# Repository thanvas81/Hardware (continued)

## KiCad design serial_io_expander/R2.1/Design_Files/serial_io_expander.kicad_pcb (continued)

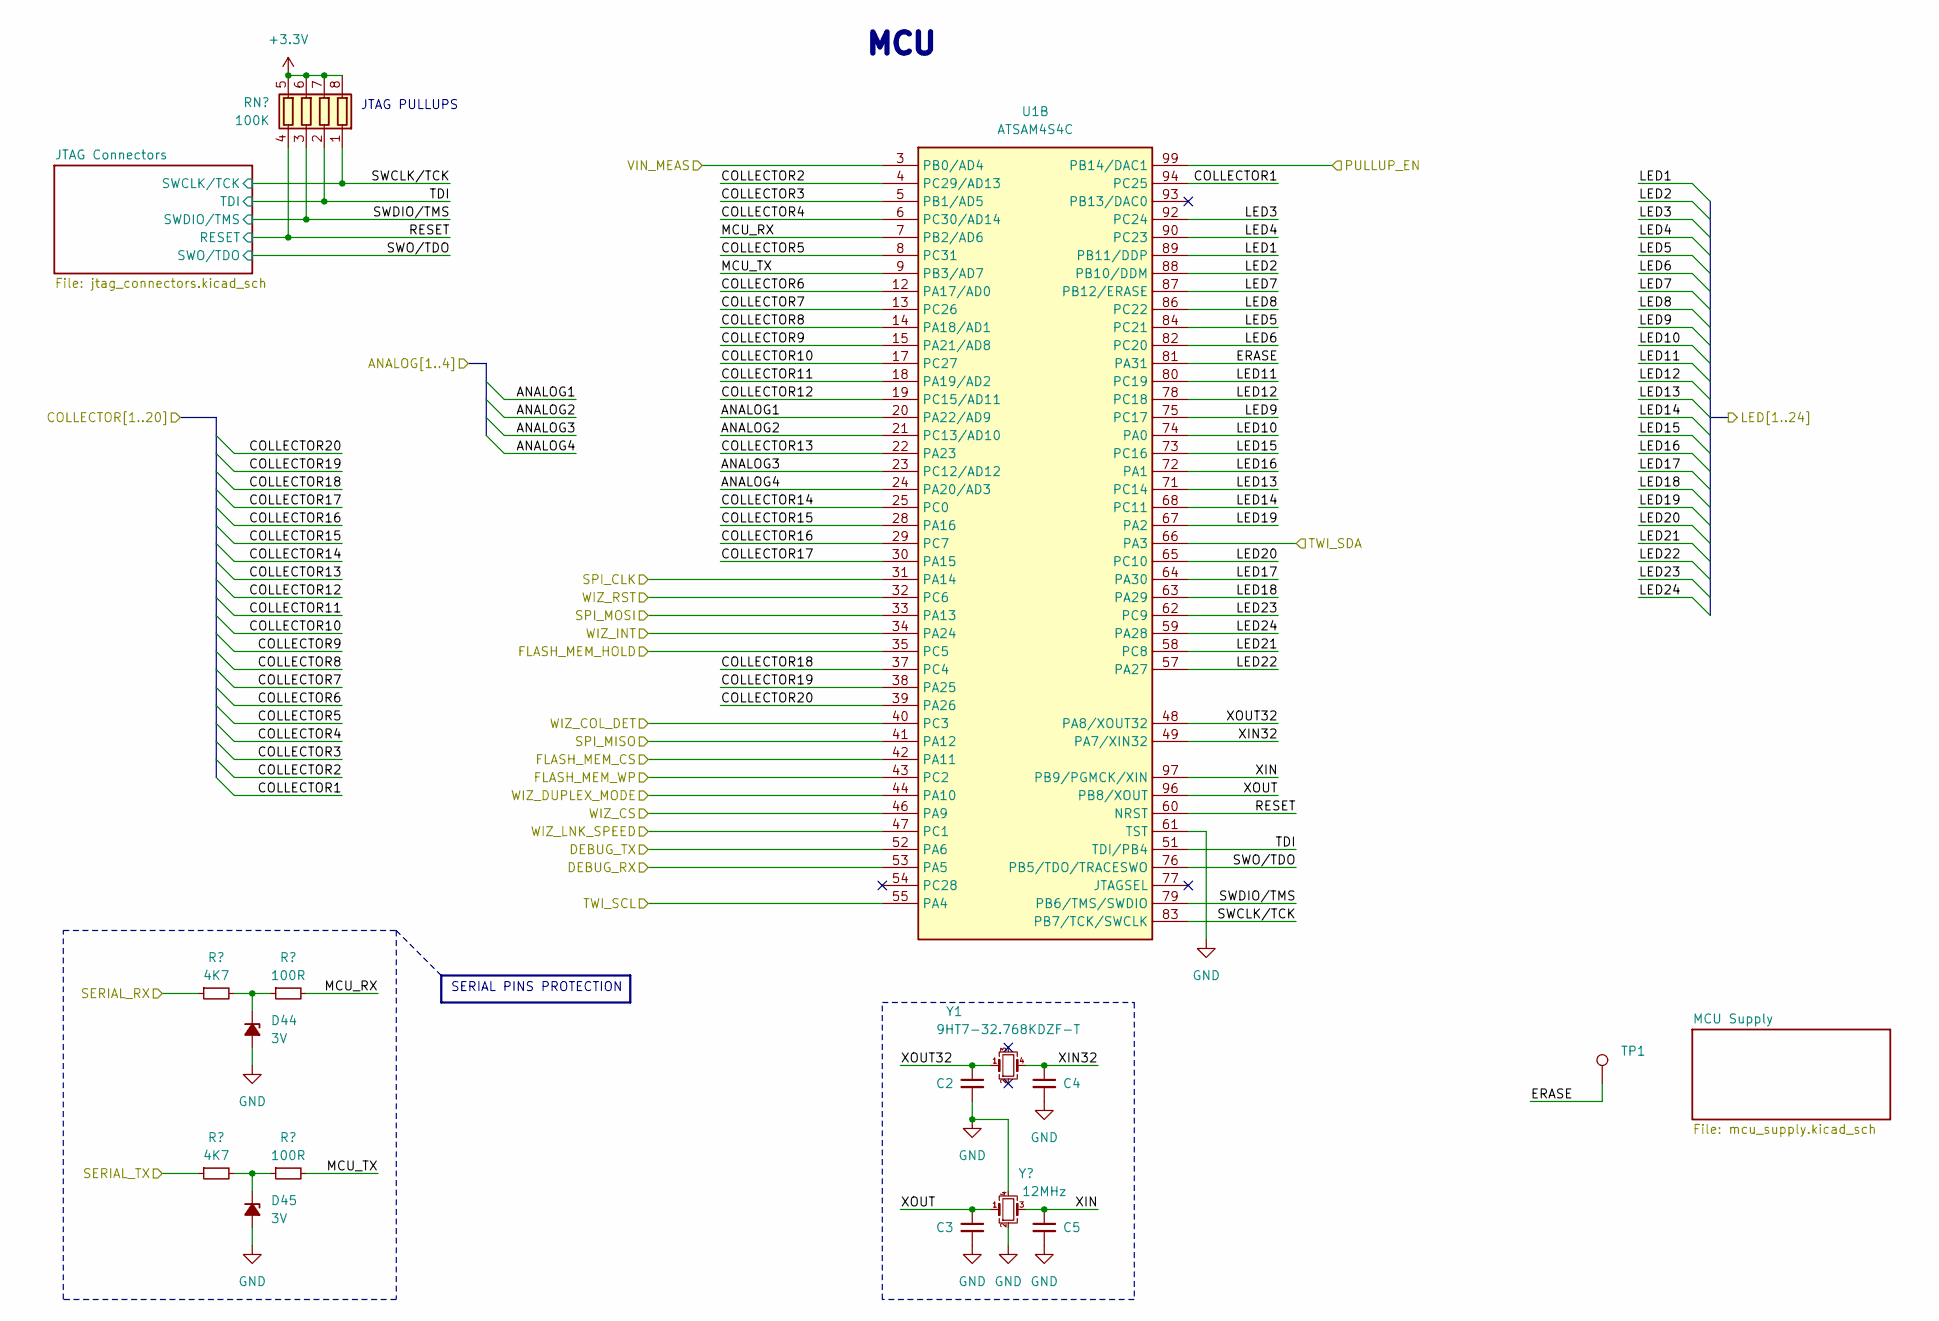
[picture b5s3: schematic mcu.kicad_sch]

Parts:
C2, C3, C4, C5: C_0603_1608Metric
D44, D45: 3V; D_SOD-123; PartkeeprID 75
R72, R73: 4K7; R_0603_1608Metric
R74, R75: 100R; R_0603_1608Metric
RN2: 100K; R_Array_Concave_4x0603
TP1: TestPoint; TestPoint_Pad_D1.5mm
U1: ATSAM4S4C; LQFP-100_14x14mm_P0.5mm
Y1: 9HT7-32.768KDZF-T; Crystal_SMD_TXC_4pin_6.9x1.4
Y2: 12MHz; Crystal_SMD_Abracon_ABM8G-4Pin_3.2x2.5mm

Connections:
/DEBUG_RX: U1.53 (PA5); also elsewhere on the board
/DEBUG_TX: U1.52 (PA6); also elsewhere on the board
/Ethernet/WIZ_CLK: U1.31 (PA14); also elsewhere on the board
/Ethernet/WIZ_COL_DET: U1.40 (PC3); also elsewhere on the board
/Ethernet/WIZ_CS: U1.46 (PA9); also elsewhere on the board
/Ethernet/WIZ_DUPLEX_MODE: U1.44 (PA10); also elsewhere on the board
/Ethernet/WIZ_INT: U1.34 (PA24); also elsewhere on the board
/Ethernet/WIZ_LNK_SPEED: U1.47 (PC1); also elsewhere on the board
/Ethernet/WIZ_MISO: U1.41 (PA12); also elsewhere on the board
/Ethernet/WIZ_MOSI: U1.33 (PA13); also elsewhere on the board
/Ethernet/WIZ_RST: U1.32 (PC6); also elsewhere on the board
/LED indicators/LED1: U1.89 (PB11/DDP); also elsewhere on the board
/LED indicators/LED2: U1.88 (PB10/DDM); also elsewhere on the board
/LED indicators/LED3: U1.92 (PC24); also elsewhere on the board
/LED indicators/LED4: U1.90 (PC23); also elsewhere on the board
/LED indicators/LED5: U1.84 (PC21); also elsewhere on the board
/LED indicators/LED6: U1.82 (PC20); also elsewhere on the board
/LED indicators/LED7: U1.87 (PB12/ERASE); also elsewhere on the board
/LED indicators/LED8: U1.86 (PC22); also elsewhere on the board
/LED indicators/LED9: U1.75 (PC17); also elsewhere on the board
/LED indicators/LED10: U1.74 (PA0); also elsewhere on the board
/LED indicators/LED11: U1.80 (PC19); also elsewhere on the board
/LED indicators/LED12: U1.78 (PC18); also elsewhere on the board
/LED indicators/LED13: U1.71 (PC14); also elsewhere on the board
/LED indicators/LED14: U1.68 (PC11); also elsewhere on the board
/LED indicators/LED15: U1.73 (PC16); also elsewhere on the board
/LED indicators/LED16: U1.72 (PA1); also elsewhere on the board
/LED indicators/LED17: U1.64 (PA30); also elsewhere on the board
/LED indicators/LED18: U1.63 (PA29); also elsewhere on the board
/LED indicators/LED19: U1.67 (PA2); also elsewhere on the board
/LED indicators/LED20: U1.65 (PC10); also elsewhere on the board
/LED indicators/LED21: U1.58 (PC8); also elsewhere on the board
/LED indicators/LED22: U1.57 (PA27); also elsewhere on the board
/LED indicators/LED23: U1.62 (PC9); also elsewhere on the board
/LED indicators/LED24: U1.59 (PA28); also elsewhere on the board
/NOR Flash/FLASH_MEM_CS: U1.42 (PA11); also elsewhere on the board
/NOR Flash/FLASH_MEM_HOLD: U1.35 (PC5); also elsewhere on the board
/NOR Flash/FLASH_MEM_WP: U1.43 (PC2); also elsewhere on the board
/SERIAL_RX: R72.1; also elsewhere on the board
/SERIAL_TX: R73.1; also elsewhere on the board
/VIN_MEAS: U1.3 (PB0/AD4); also elsewhere on the board
/digital_inputs/COLLECTOR1: U1.94 (PC25); also elsewhere on the board
/digital_inputs/COLLECTOR2: U1.4 (PC29/AD13); also elsewhere on the board
/digital_inputs/COLLECTOR3: U1.5 (PB1/AD5); also elsewhere on the board
/digital_inputs/COLLECTOR4: U1.6 (PC30/AD14); also elsewhere on the board
/digital_inputs/COLLECTOR5: U1.8 (PC31); also elsewhere on the board
/digital_inputs/COLLECTOR6: U1.12 (PA17/AD0); also elsewhere on the board
/digital_inputs/COLLECTOR7: U1.13 (PC26); also elsewhere on the board
/digital_inputs/COLLECTOR8: U1.14 (PA18/AD1); also elsewhere on the board
/digital_inputs/COLLECTOR9: U1.15 (PA21/AD8); also elsewhere on the board
/digital_inputs/COLLECTOR10: U1.17 (PC27); also elsewhere on the board
/digital_inputs/COLLECTOR11: U1.18 (PA19/AD2); also elsewhere on the board
/digital_inputs/COLLECTOR12: U1.19 (PC15/AD11); also elsewhere on the board
/digital_inputs/COLLECTOR13: U1.22 (PA23); also elsewhere on the board
/digital_inputs/COLLECTOR14: U1.25 (PC0); also elsewhere on the board
/digital_inputs/COLLECTOR15: U1.28 (PA16); also elsewhere on the board
/digital_inputs/COLLECTOR16: U1.29 (PC7); also elsewhere on the board
/digital_inputs/COLLECTOR17: U1.30 (PA15); also elsewhere on the board
/digital_inputs/COLLECTOR18: U1.37 (PC4); also elsewhere on the board
/digital_inputs/COLLECTOR19: U1.38 (PA25); also elsewhere on the board
/digital_inputs/COLLECTOR20: U1.39 (PA26); also elsewhere on the board
/digital_inputs/PULLUP_EN: U1.99 (PB14/DAC1); also elsewhere on the board
/mcu/ANALOG1: U1.20 (PA22/AD9); also elsewhere on the board
/mcu/ANALOG2: U1.21 (PC13/AD10); also elsewhere on the board
/mcu/ANALOG3: U1.23 (PC12/AD12); also elsewhere on the board
/mcu/ANALOG4: U1.24 (PA20/AD3); also elsewhere on the board
/mcu/MCU_RX: R74.2, U1.7 (PB2/AD6)
/mcu/MCU_TX: R75.2, U1.9 (PB3/AD7)
/mcu/RESET: RN2.4 (R4.1), U1.60 (NRST); also elsewhere on the board
/mcu/SWCLK/TCK: RN2.1 (R1.1), U1.83 (PB7/TCK/SWCLK); also elsewhere on the board
/mcu/SWDIO/TMS: RN2.3 (R3.1), U1.79 (PB6/TMS/SWDIO); also elsewhere on the board
/mcu/SWO/TDO: U1.76 (PB5/TDO/TRACESWO); also elsewhere on the board
/mcu/TDI: RN2.2 (R2.1), U1.51 (TDI/PB4); also elsewhere on the board
/mcu/XIN: C5.1, U1.97 (PB9/PGMCK/XIN), Y2.3
/mcu/XIN32: C4.1, U1.49 (PA7/XIN32), Y1.4
/mcu/XOUT: C3.1, U1.96 (PB8/XOUT), Y2.1
/mcu/XOUT32: C2.1, U1.48 (PA8/XOUT32), Y1.1
GND: C2.2, C3.2, C4.2, C5.2, D44.2 (A), D45.2 (A), U1.61 (TST), Y2.2, Y2.4; also elsewhere on the board
unnamed: D44.1 (K), R72.2, R74.1
unnamed: D45.1 (K), R73.2, R75.1

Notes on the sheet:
JTAG PULLUPS
${TITLE}
SERIAL PINS PROTECTION

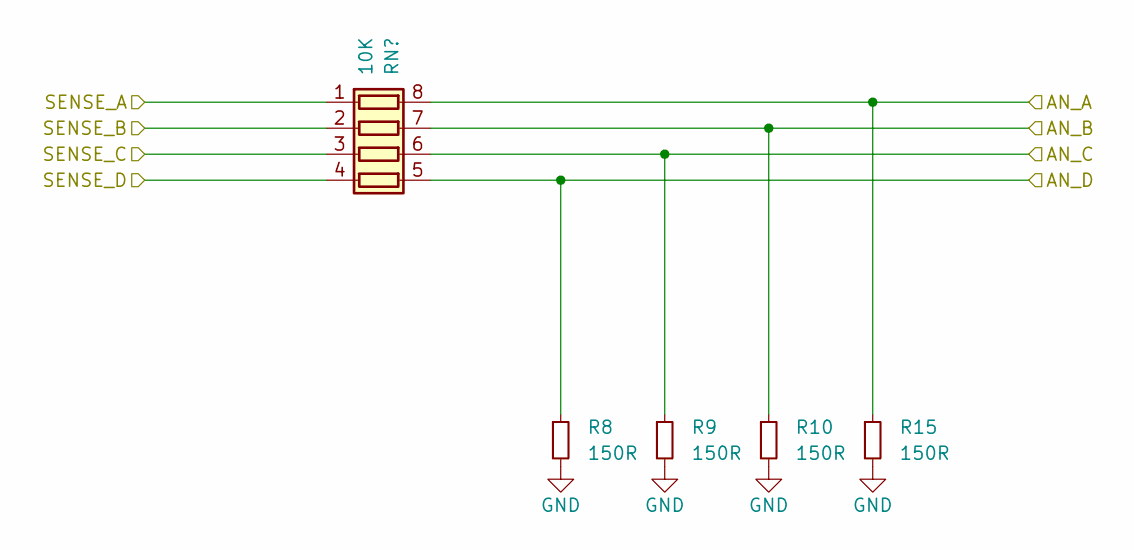
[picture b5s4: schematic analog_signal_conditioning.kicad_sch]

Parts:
R8, R9, R10, R15: 150R; R_2512_6332Metric
RN20: 10K; R_Array_Concave_4x0603

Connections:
/analog_signal_conditioning/AN_A: R15.1, RN20.8 (R1.2); also elsewhere on the board
/analog_signal_conditioning/AN_B: R10.1, RN20.7 (R2.2); also elsewhere on the board
/analog_signal_conditioning/AN_C: R9.1, RN20.6 (R3.2); also elsewhere on the board
/analog_signal_conditioning/AN_D: R8.1, RN20.5 (R4.2); also elsewhere on the board
/mcu/ANALOG1: RN20.4 (R4.1); also elsewhere on the board
/mcu/ANALOG2: RN20.3 (R3.1); also elsewhere on the board
/mcu/ANALOG3: RN20.2 (R2.1); also elsewhere on the board
/mcu/ANALOG4: RN20.1 (R1.1); also elsewhere on the board
GND: R8.2, R9.2, R10.2, R15.2; also elsewhere on the board

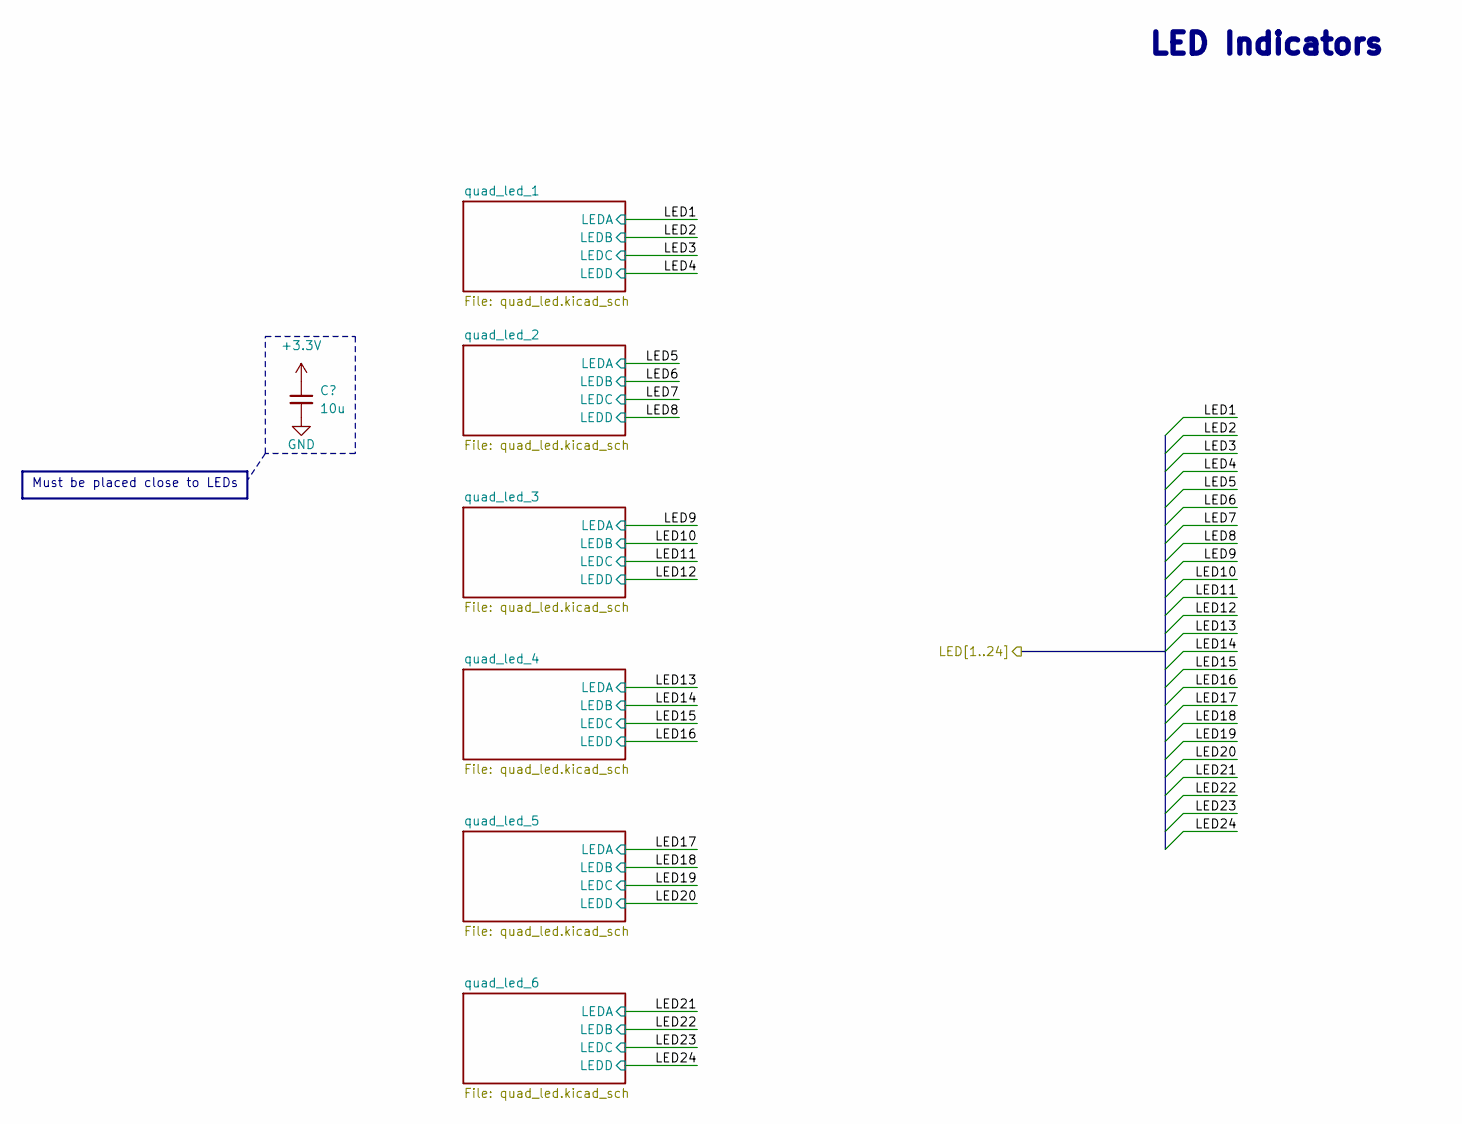
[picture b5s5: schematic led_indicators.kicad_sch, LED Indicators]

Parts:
C13: 10u; C_0805_2012Metric; PartkeeprID 52

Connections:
GND: C13.2; also elsewhere on the board

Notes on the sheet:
Must be placed close to LEDs
${TITLE}

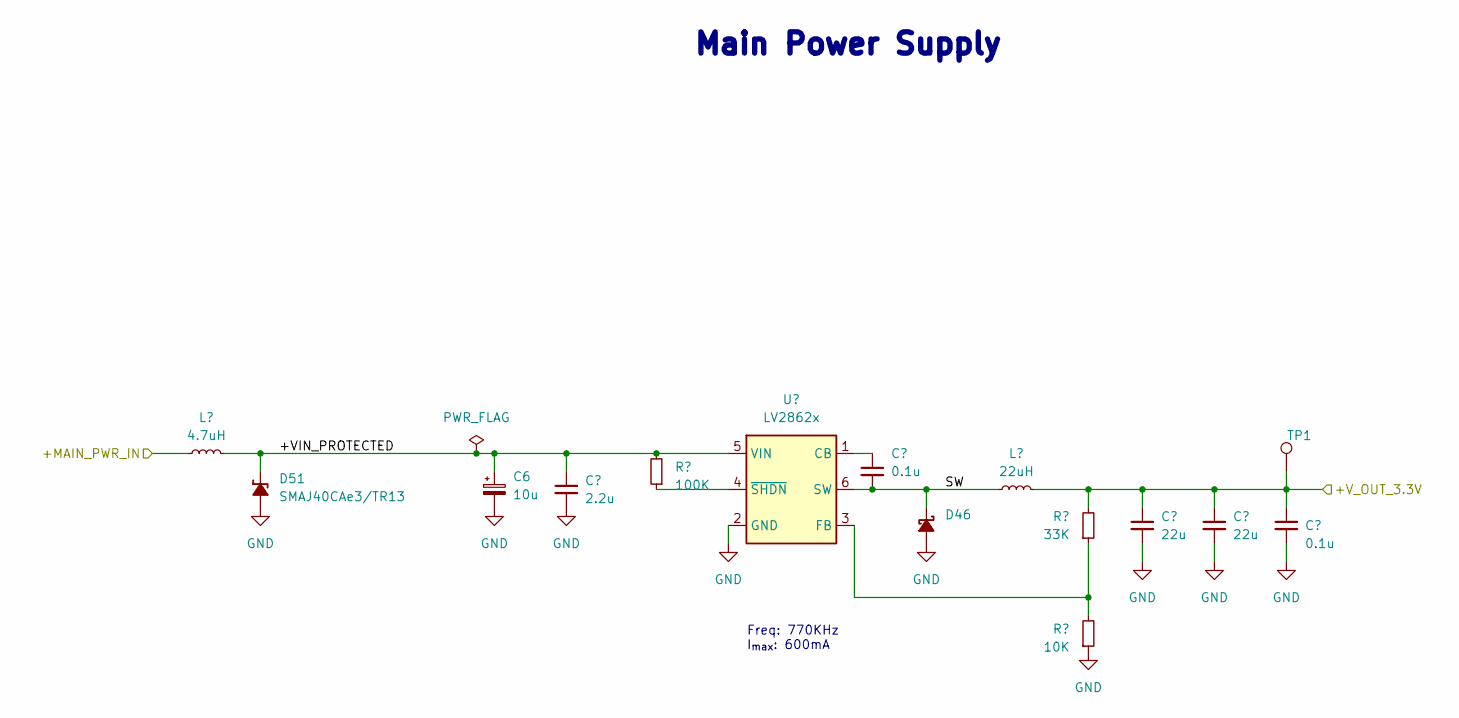
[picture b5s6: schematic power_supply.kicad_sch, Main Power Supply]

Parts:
C6: 10u; CP_Elec_5x5.3; PartkeeprID 41
C7: 2.2u; C_1210_3225Metric; PartkeeprID 42
C8, C11: 0.1u; C_0603_1608Metric; PartkeeprID 50
C9, C10: 22u; C_1210_3225Metric; PartkeeprID 45
D46: SBR3U60P1Q-7; D_PowerDI-123; PartkeeprID 43
D51: SMAJ40CAe3/TR13; D_SMA
L1: 22uH; L_Taiyo-Yuden_NR-50xx; PartkeeprID 44
L5: 4.7uH; L_TDK_VLS252012HBX; PartkeeprID 44
R76: 100K; R_0603_1608Metric; PartkeeprID 47
R77: 33K; R_0603_1608Metric; PartkeeprID 49
R78: 10K; R_0603_1608Metric; PartkeeprID 48
TP1: TestPoint; TestPoint_Pad_D1.5mm
U2: LV2862x; SOT-23-6; PartkeeprID 46

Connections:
+VIN: L5.1; also elsewhere on the board
/power supply/+VIN_PROTECTED: C6.1, C7.1, D51.1 (K), L5.2, R76.2, U2.5 (VIN)
/power supply/SW: C8.2, D46.1 (K), L1.1, U2.6 (SW)
GND: C6.2, C7.2, C9.2, C10.2, C11.2, D46.2 (A), D51.2 (A), R78.1, U2.2 (GND); also elsewhere on the board
unnamed: C8.1, U2.1 (CB)
unnamed: R77.1, R78.2, U2.3 (FB)
unnamed: R76.1, U2.4 (~SHDN)

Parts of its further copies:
TP2: TestPoint; TestPoint_Pad_D1.5mm

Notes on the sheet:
Freq: 770KHz I_{max}: 600mA
${TITLE}

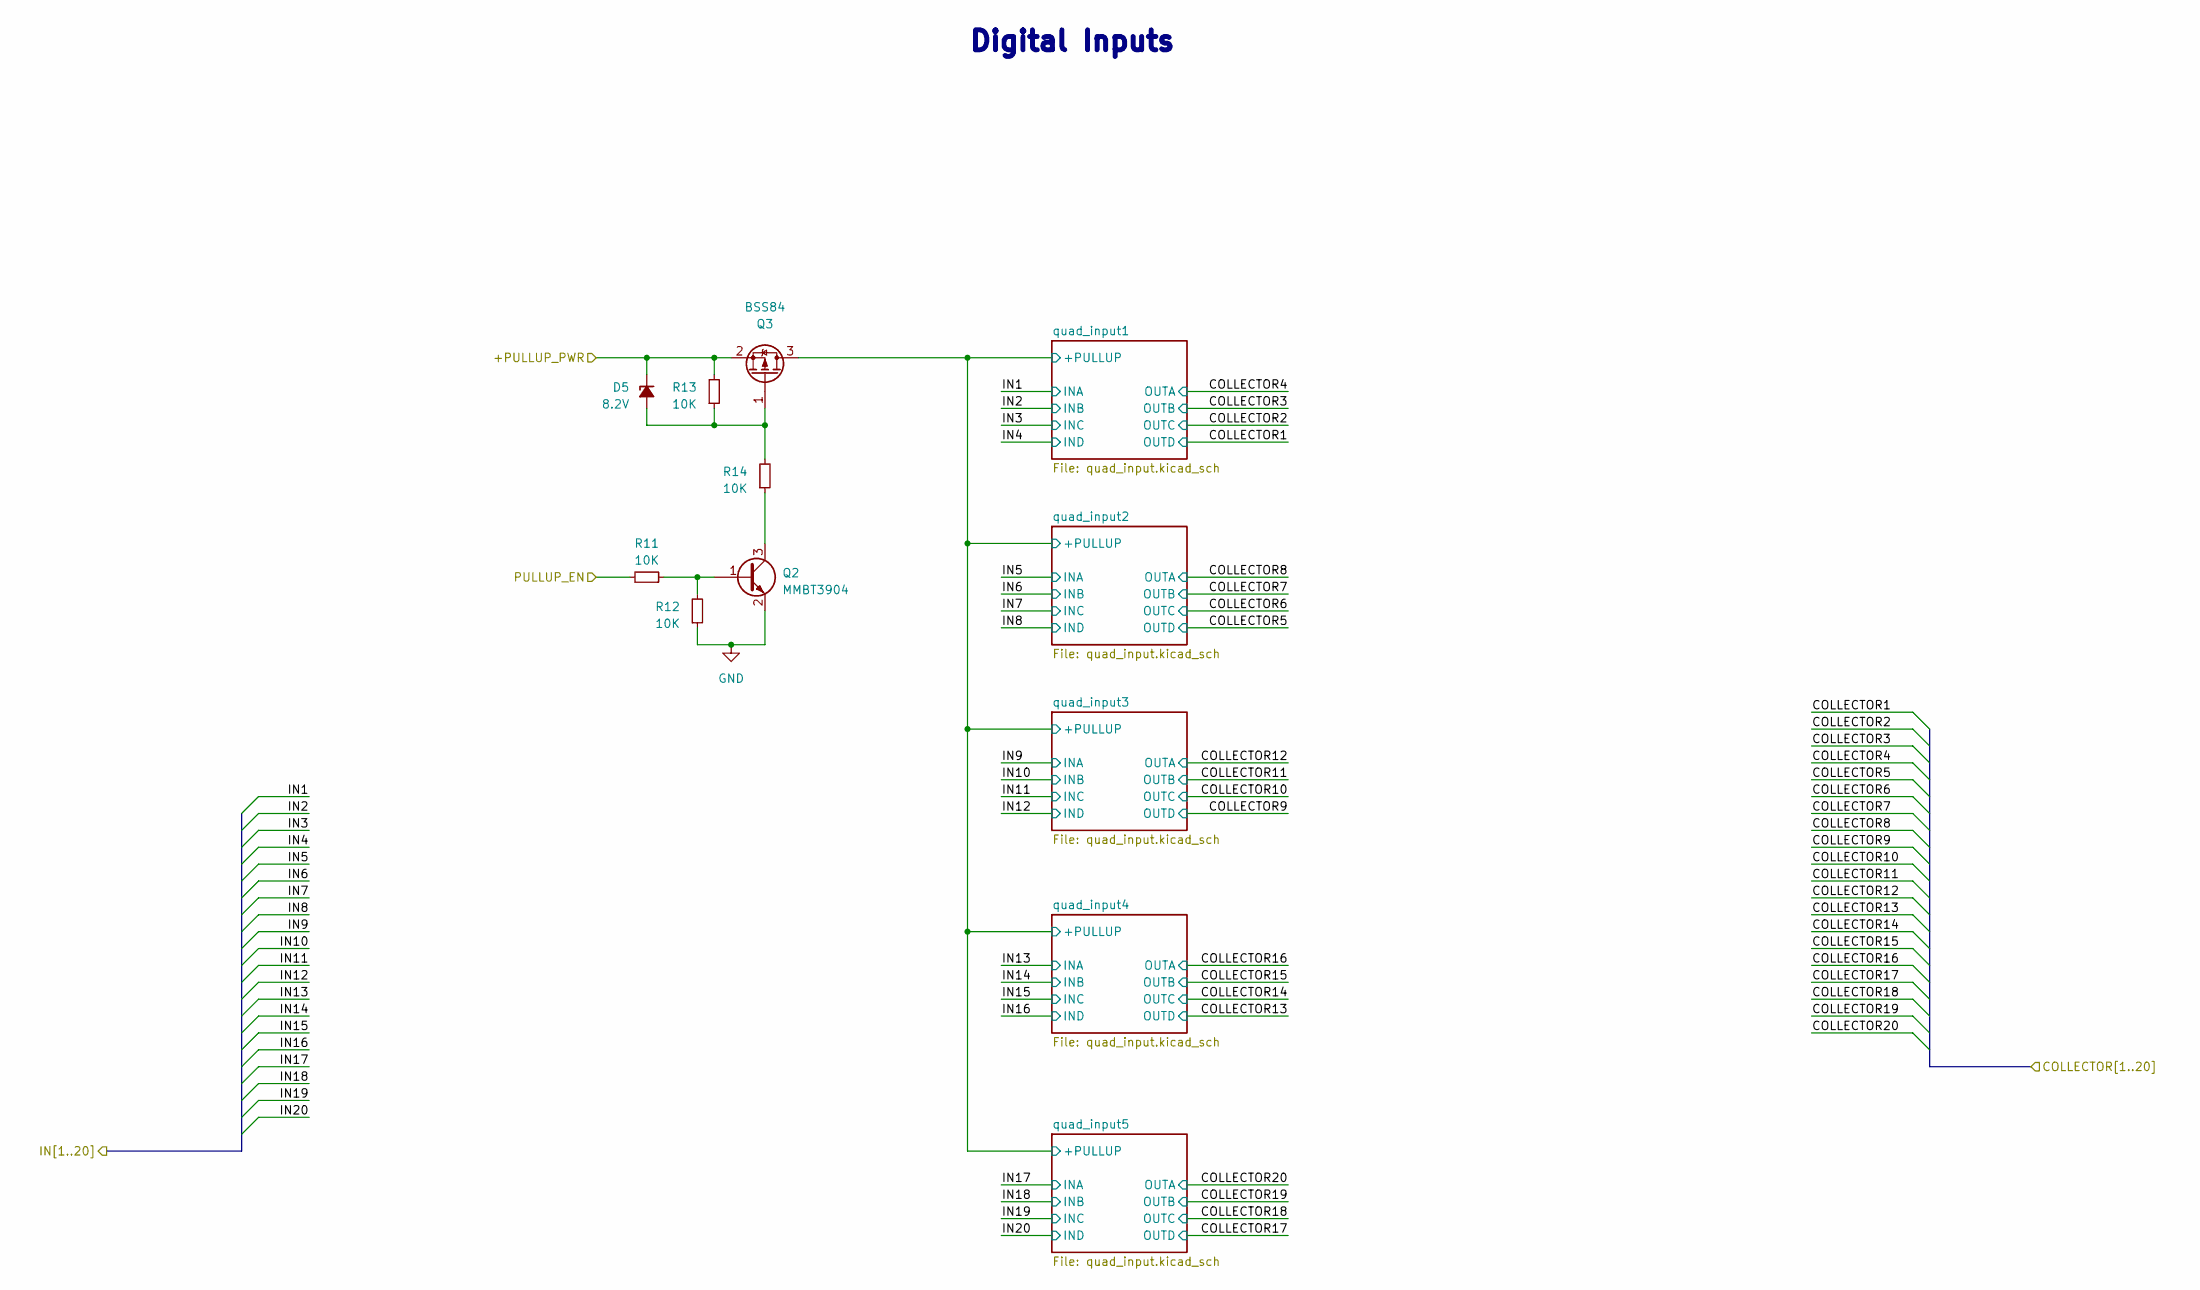
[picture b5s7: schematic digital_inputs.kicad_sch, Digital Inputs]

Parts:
D5: 8.2V; D_SOD-123F; Part No BZT52C8V2-TP
Q2: MMBT3904; SOT-23; Part No MMBT3904-TP
Q3: BSS84; SOT-23; Part No BSS84AK,215
R11, R12, R13, R14: 10K; R_0603_1608Metric

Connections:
+VIN: D5.1 (K), Q3.2 (S), R13.2; also elsewhere on the board
/digital_inputs/PULLUP_EN: R11.2; also elsewhere on the board
/digital_inputs/quad_input1/+PULLUP: Q3.3 (D); also elsewhere on the board
GND: Q2.2 (E), R12.1; also elsewhere on the board
unnamed: D5.2 (A), Q3.1 (G), R13.1, R14.2
unnamed: Q2.1 (B), R11.1, R12.2
unnamed: Q2.3 (C), R14.1

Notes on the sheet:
${TITLE}

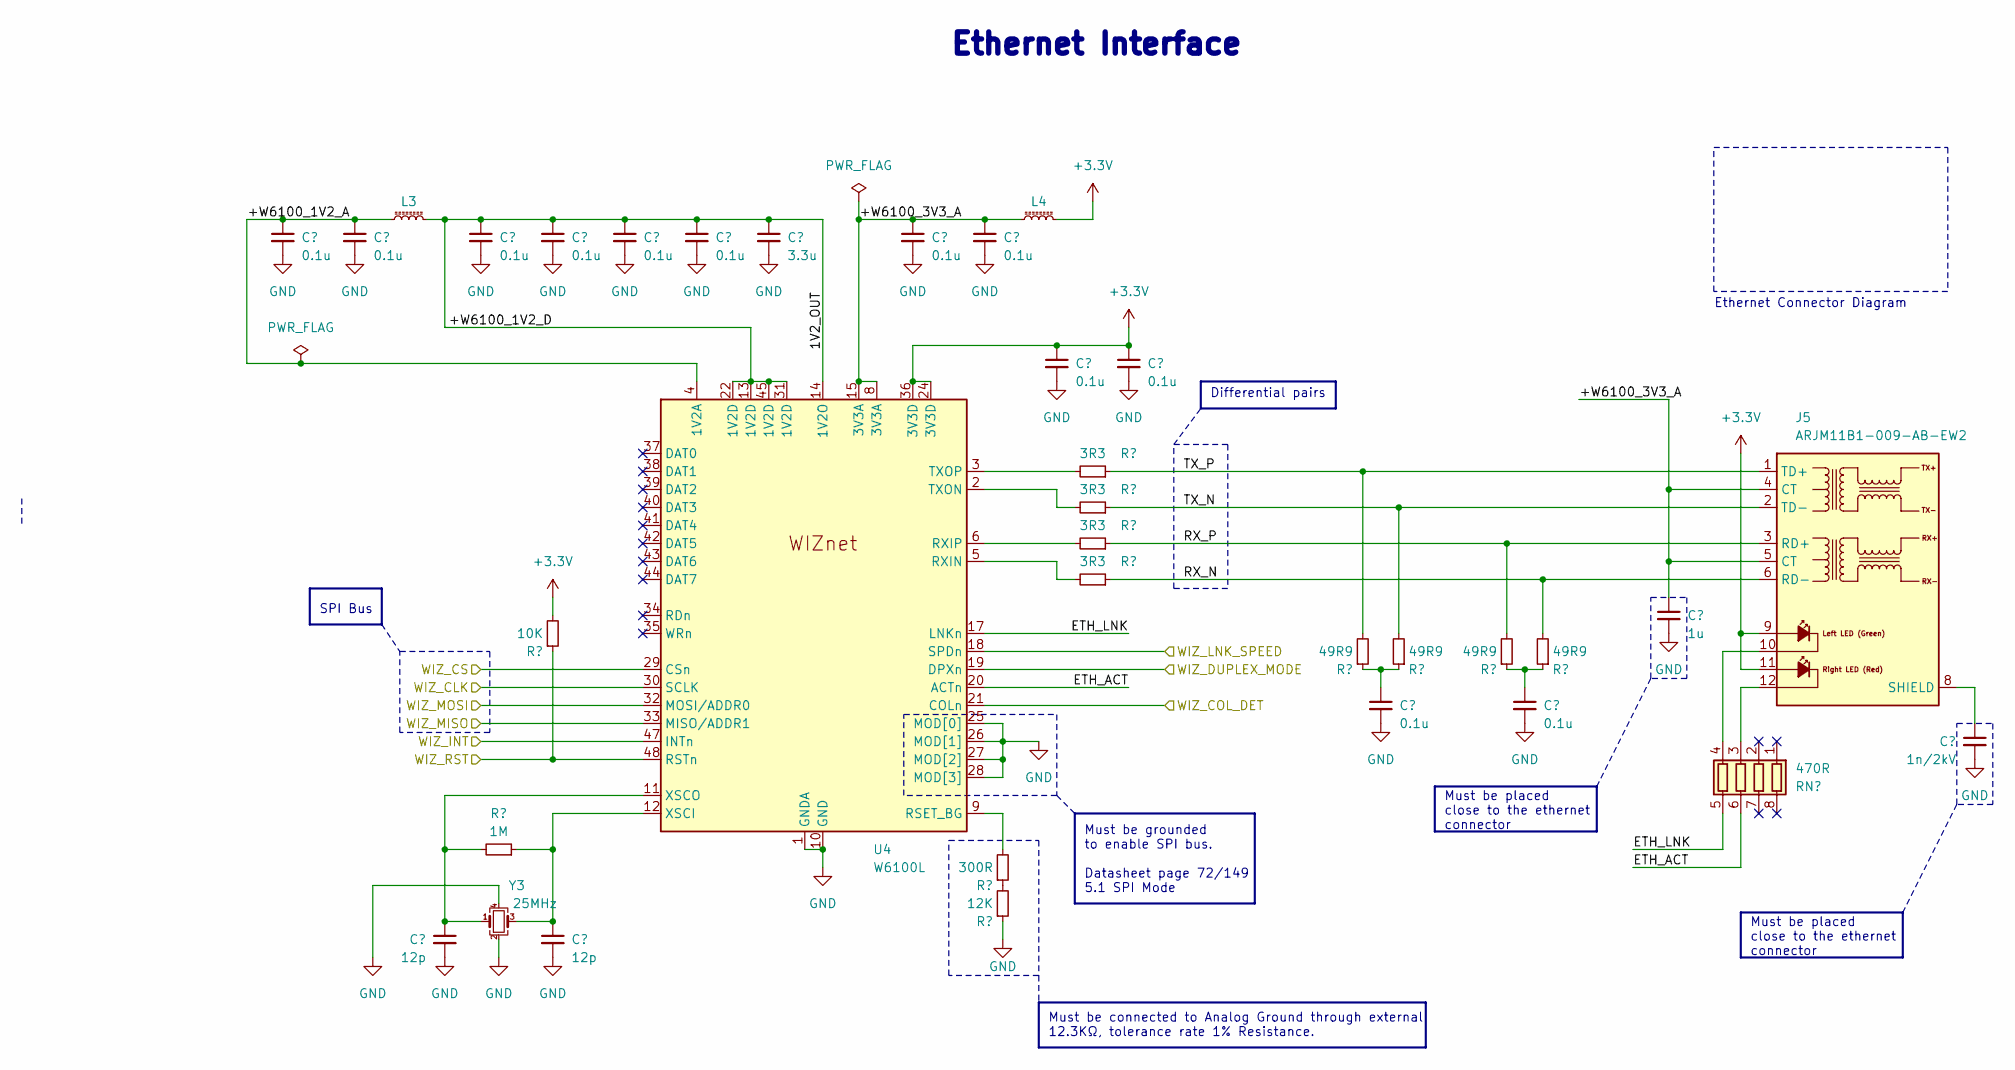
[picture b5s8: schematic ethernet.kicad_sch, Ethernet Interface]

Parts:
C31, C32, C34, C35, C37, C38, C40, C41, C42, C43, C44, C45: 0.1u; C_0603_1608Metric; PartkeeprID 50
C33, C36: 12p; C_0603_1608Metric; PartkeeprID 50
C39: 3.3u; C_0603_1608Metric
C46: 1u; C_0805_2012Metric; PartkeeprID 50
C47: 1n/2kV; C_1206_3216Metric; PartkeeprID 50
J5: ARJM11B1-009-AB-EW2; ARJM11B1-009-AB-EW2_Horizontal
L3, L4: L_Ferrite_Small; L_0603_1608Metric
R79: 1M; R_0402_1005Metric
R80: 10K; R_0603_1608Metric
R81: 300R; R_0402_1005Metric
R82: 12K; R_0402_1005Metric
R83, R84, R85, R86: 3R3; R_0402_1005Metric
R87, R88, R89, R90: 49R9; R_0402_1005Metric
RN1: 470R; R_Array_Concave_4x0603
U4: W6100L; LQFP-48_7x7mm_P0.5mm
Y3: 25MHz; Crystal_SMD_3225-4Pin_3.2x2.5mm

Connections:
/Ethernet/+W6100_1V2_A: C31.1, C32.1, L3.2, U4.4 (1V2A)
/Ethernet/+W6100_1V2_D: C34.1, C35.1, C37.1, C38.1, C39.1, L3.1, U4.13 (1V2D), U4.14 (1V2O), U4.22 (1V2D), U4.31 (1V2D), U4.45 (1V2D)
/Ethernet/+W6100_3V3_A: C40.1, C41.1, C46.1, J5.4 (CT), J5.5 (CT), L4.1, U4.8 (3V3A), U4.15 (3V3A)
/Ethernet/RX_N: J5.6 (RD-), R86.1, R90.2
/Ethernet/RX_P: J5.3 (RD+), R85.1, R89.2
/Ethernet/TX_N: J5.2 (TD-), R84.1, R88.2
/Ethernet/TX_P: J5.1 (TD+), R83.1, R87.2
/Ethernet/WIZ_CLK: U4.30 (SCLK); also elsewhere on the board
/Ethernet/WIZ_COL_DET: U4.21 (COLn); also elsewhere on the board
/Ethernet/WIZ_CS: U4.29 (CSn); also elsewhere on the board
/Ethernet/WIZ_DUPLEX_MODE: U4.19 (DPXn); also elsewhere on the board
/Ethernet/WIZ_INT: U4.47 (INTn); also elsewhere on the board
/Ethernet/WIZ_LNK_SPEED: U4.18 (SPDn); also elsewhere on the board
/Ethernet/WIZ_MISO: U4.33 (MISO/ADDR1); also elsewhere on the board
/Ethernet/WIZ_MOSI: U4.32 (MOSI/ADDR0); also elsewhere on the board
/Ethernet/WIZ_RST: R80.1, U4.48 (RSTn); also elsewhere on the board
GND: C31.2, C32.2, C33.2, C34.2, C35.2, C36.2, C37.2, C38.2, C39.2, C40.2, C41.2, C42.2, C43.2, C44.2, C45.2, C46.2, C47.2, R82.1, U4.1 (GNDA), U4.7 (GNDA), U4.10 (GND), U4.16 (GNDA), U4.23 (GND), U4.25 (MOD[0]), U4.26 (MOD[1]), U4.27 (MOD[2]), U4.28 (MOD[3]), U4.46 (GND), Y3.2, Y3.4; also elsewhere on the board
unnamed: C44.1, R87.1, R88.1
unnamed: C45.1, R89.1, R90.1
unnamed: C47.1, J5.8 (SHIELD)
unnamed: R81.1, R82.2
unnamed: R81.2, U4.9 (RSET_BG)
unnamed: R86.2, U4.5 (RXIN)
unnamed: R85.2, U4.6 (RXIP)
unnamed: R84.2, U4.2 (TXON)
unnamed: R83.2, U4.3 (TXOP)
unnamed: C36.1, R79.1, U4.12 (XSCI), Y3.3
unnamed: C33.1, R79.2, U4.11 (XSCO), Y3.1

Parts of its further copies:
RN8: 470R; R_Array_Concave_4x0603

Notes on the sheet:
${TITLE}
Must be connected to Analog Ground through external 12.3KΩ, tolerance rate 1% Resistance.
Must be placed close to the ethernet connector
SPI Bus
Must be grounded to enable SPI bus. Datasheet page 72/149 5.1 SPI Mode
Differential pairs
Ethernet Connector Diagram

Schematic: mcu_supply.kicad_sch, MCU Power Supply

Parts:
C14, C20, C26, C28: 4.7u; C_0805_2012Metric
C15, C16, C17, C19, C21, C22, C23, C24, C25, C27, C29, C30: 0.1u; C_0603_1608Metric; PartkeeprID 50
C18: 10u; C_0805_2012Metric; PartkeeprID 52
L2: 10uH; L_0603_1608Metric
U1: ATSAM4S4C; LQFP-100_14x14mm_P0.5mm

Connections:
/mcu/MCU Supply/+VDDCORE: C24.1, C26.1, C27.1, C29.1, C30.1, L2.2, U1.11 (VDDOUT), U1.16 (VDDCORE), U1.36 (VDDCORE), U1.56 (VDDCORE), U1.85 (VDDCORE)
/mcu/MCU Supply/+VDDPLL: C25.1, C28.1, L2.1, U1.100 (VDDPLL)
GND: C14.2, C15.2, C16.2, C17.2, C18.2, C19.2, C20.2, C21.2, C22.2, C23.2, C24.2, C25.2, C26.2, C27.2, C28.2, C29.2, C30.2, U1.2 (GND), U1.26 (GND), U1.45 (GND), U1.70 (GND), U1.95 (GND); also elsewhere on the board

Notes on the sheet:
${TITLE}

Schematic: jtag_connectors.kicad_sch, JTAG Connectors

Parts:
J6: HeaderPin_ARM_JTAG_SWD_10; PinHeader_2x05_P2.54mm_Vertical
J7: TC2050_Connector; Tag-Connect_TC2050-IDC-NL_2x05_P1.27mm_Vertical

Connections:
/mcu/RESET: J6.10 (~RESET), J7.10 (RST); also elsewhere on the board
/mcu/SWCLK/TCK: J6.4 (SWCLK/TCK), J7.4 (SWCLK/TCK); also elsewhere on the board
/mcu/SWDIO/TMS: J6.2 (SWDIO/TMS), J7.2 (SWDIO/TMS); also elsewhere on the board
/mcu/SWO/TDO: J6.6 (SWO/TDO), J7.6 (SWO/TDO); also elsewhere on the board
/mcu/TDI: J6.8 (NC/TDI), J7.8 (TDI); also elsewhere on the board
GND: J6.3 (GND), J6.5 (GND), J6.9 (GNDDetect), J7.3 (GND), J7.5 (GND); also elsewhere on the board

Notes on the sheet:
${TITLE}

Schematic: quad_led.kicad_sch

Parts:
D47, D50, D53, D56: LED_Small_Filled; LED_0603_1608Metric
RN3: R_Pack04_Split; R_Array_Concave_4x0603
U7: PUMH11,115; SOT-363_SC-70-6

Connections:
/LED indicators/LED13: U7.2; also elsewhere on the board
/LED indicators/LED14: U7.5; also elsewhere on the board
GND: U7.1, U7.4; also elsewhere on the board

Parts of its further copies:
D24, D25, D26, D27, D28, D29, D30, D31, D32, D33, D34, D35, D36, D37, D38, D39, D40, D41, D42, D43, D48, D49: LED_Small_Filled; LED_0603_1608Metric
RN4, RN5, RN6, RN7, RN19: R_Pack04_Split; R_Array_Concave_4x0603
U8, U9, U10, U11, U12, U13, U14, U17, U18, U19, U20: PUMH11,115; SOT-363_SC-70-6

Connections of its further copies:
/LED indicators/LED1: U19.2; also elsewhere on the board
/LED indicators/LED2: U19.5; also elsewhere on the board
/LED indicators/LED3: U20.2; also elsewhere on the board
/LED indicators/LED4: U20.5; also elsewhere on the board
/LED indicators/LED5: U8.2; also elsewhere on the board
/LED indicators/LED6: U8.5; also elsewhere on the board
/LED indicators/LED7: U9.2; also elsewhere on the board
/LED indicators/LED8: U9.5; also elsewhere on the board
/LED indicators/LED9: U11.2; also elsewhere on the board
/LED indicators/LED10: U11.5; also elsewhere on the board
/LED indicators/LED11: U12.2; also elsewhere on the board
/LED indicators/LED12: U12.5; also elsewhere on the board
/LED indicators/LED15: U10.2; also elsewhere on the board
/LED indicators/LED16: U10.5; also elsewhere on the board
/LED indicators/LED17: U13.2; also elsewhere on the board
/LED indicators/LED18: U13.5; also elsewhere on the board
/LED indicators/LED19: U14.2; also elsewhere on the board
/LED indicators/LED20: U14.5; also elsewhere on the board
/LED indicators/LED21: U17.2; also elsewhere on the board
/LED indicators/LED22: U17.5; also elsewhere on the board
/LED indicators/LED23: U18.2; also elsewhere on the board
/LED indicators/LED24: U18.5; also elsewhere on the board
GND: U8.1, U8.4, U9.1, U9.4, U10.1, U10.4, U11.1, U11.4, U12.1, U12.4, U13.1, U13.4, U14.1, U14.4, U17.1, U17.4, U18.1, U18.4, U19.1, U19.4, U20.1, U20.4; also elsewhere on the board
unnamed: D24.1 (K), RN19.1 (R1.1)
unnamed: D25.1 (K), RN19.2 (R2.1)
unnamed: D32.1 (K), RN4.1 (R1.1)
unnamed: D33.1 (K), RN4.2 (R2.1)
unnamed: D34.1 (K), RN4.3 (R3.1)
unnamed: D35.1 (K), RN4.4 (R4.1)
unnamed: D36.1 (K), RN5.1 (R1.1)
unnamed: D37.1 (K), RN5.2 (R2.1)
unnamed: D38.1 (K), RN5.3 (R3.1)
unnamed: D39.1 (K), RN5.4 (R4.1)
unnamed: D40.1 (K), RN6.1 (R1.1)
unnamed: D41.1 (K), RN6.2 (R2.1)
unnamed: D42.1 (K), RN6.3 (R3.1)
unnamed: D43.1 (K), RN6.4 (R4.1)
unnamed: D48.1 (K), RN7.2 (R2.1)
unnamed: D49.1 (K), RN7.3 (R3.1)
unnamed: RN4.8 (R1.2), U11.6
unnamed: RN4.7 (R2.2), U11.3
unnamed: RN4.6 (R3.2), U12.6
unnamed: RN4.5 (R4.2), U12.3
unnamed: RN5.8 (R1.2), U13.6
unnamed: RN5.7 (R2.2), U13.3
unnamed: RN5.6 (R3.2), U14.6
unnamed: RN5.5 (R4.2), U14.3
unnamed: RN6.8 (R1.2), U17.6
unnamed: RN6.7 (R2.2), U17.3
unnamed: RN6.6 (R3.2), U18.6
unnamed: RN6.5 (R4.2), U18.3
unnamed: RN7.8 (R1.2), U19.6
unnamed: RN7.7 (R2.2), U19.3
unnamed: RN7.6 (R3.2), U20.6
unnamed: RN7.5 (R4.2), U20.3
unnamed: RN19.8 (R1.2), U8.6
unnamed: RN19.7 (R2.2), U8.3
unnamed: RN19.6 (R3.2), U9.6
unnamed: RN19.5 (R4.2), U9.3
